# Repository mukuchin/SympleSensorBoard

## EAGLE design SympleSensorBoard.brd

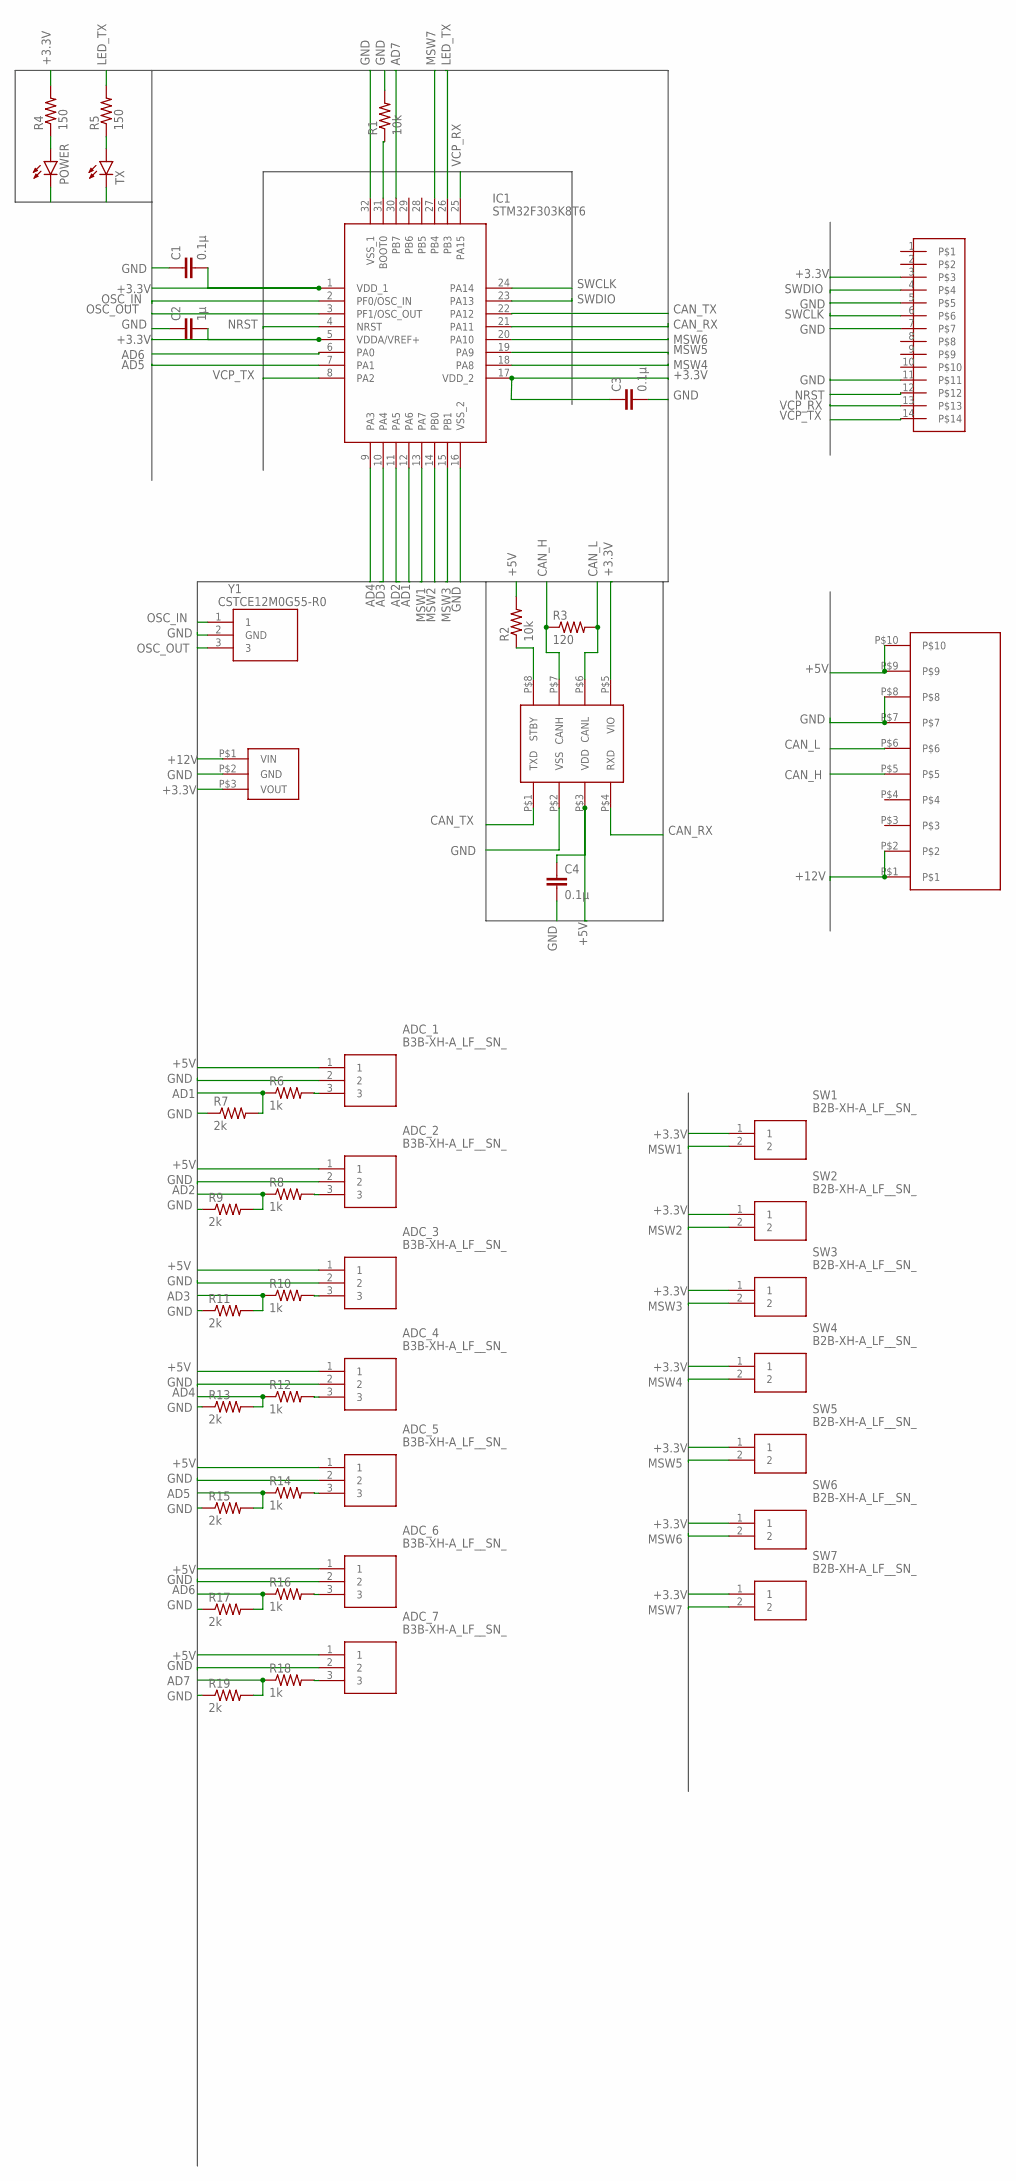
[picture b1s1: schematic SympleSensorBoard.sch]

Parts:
ADC_1, ADC_2, ADC_3, ADC_4, ADC_5, ADC_6, ADC_7: B3B-XH-A_LF__SN_; SHDR3W64P0X250_1X3_990X575X700
C1, C3, C4: 0.1μ; C0603
C2: 1μ; C0603
IC1: STM32F303K8T6; QFP80P900X900X160-32N
POWER: LEDCHIP-LED0603; CHIP-LED0603
R1, R2: 10k; R0603
R3: 120; R0603
R4, R5: 150; R0603
R6, R8, R10, R12, R14, R16, R18: 1k; R0603
R7, R9, R11, R13, R15, R17, R19: 2k; R0603
SW1, SW2, SW3, SW4, SW5, SW6, SW7: B2B-XH-A_LF__SN_; SHDR2W64P0X250_1X2_740X575X700
TX: LEDCHIP-LED0603; CHIP-LED0603
U$1: BP5293-33; DC/DC_REGULATOR_3P
U$2: MCP2562MCP2561-SN; SOIC8
U$3: BOX14P; CON_HEDA14P_1.27
U$4: BOX10PBOX10P-L; BOX10P-L
Y1: CSTCE12M0G55-R0

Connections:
+3.3V: C1.2, C2.2, C3.1, IC1.1 (VDD_1), IC1.5 (VDDA/VREF+), IC1.17 (VDD_2), R4.2, SW1.1, SW2.1, SW3.1, SW4.1, SW5.1, SW6.1, SW7.1, U$1.P$3 (VOUT), U$2.P$5 (VIO), U$3.3
+5V: ADC_1.1, ADC_2.1, ADC_3.1, ADC_4.1, ADC_5.1, ADC_6.1, ADC_7.1, C4.1, R2.2, U$2.P$3 (VDD), U$4.P$9, U$4.P$10
+12V: U$1.P$1 (VIN), U$4.P$1, U$4.P$2
AD1: IC1.12 (PA6), R6.1, R7.2
AD2: IC1.11 (PA5), R8.1, R9.2
AD3: IC1.10 (PA4), R10.1, R11.2
AD4: IC1.9 (PA3), R12.1, R13.2
AD5: IC1.7 (PA1), R14.1, R15.2
AD6: IC1.6 (PA0), R16.1, R17.2
AD7: IC1.30 (PB7), R18.1, R19.2
CAN_H: R3.1, U$2.P$7 (CANH), U$4.P$5
CAN_L: R3.2, U$2.P$6 (CANL), U$4.P$6
CAN_RX: IC1.21 (PA11), U$2.P$4 (RXD)
CAN_TX: IC1.22 (PA12), U$2.P$1 (TXD)
GND: ADC_1.2, ADC_2.2, ADC_3.2, ADC_4.2, ADC_5.2, ADC_6.2, ADC_7.2, C1.1, C2.1, C3.2, C4.2, IC1.16 (VSS_2), IC1.32 (VSS_1), POWER.C, R1.2, R7.1, R9.1, R11.1, R13.1, R15.1, R17.1, R19.1, TX.C, U$1.P$2 (GND), U$2.P$2 (VSS), U$3.5, U$3.7, U$3.11, U$4.P$7, U$4.P$8, Y1.2 (GND)
LED_TX: IC1.26 (PB3), R5.2
MSW1: IC1.13 (PA7), SW1.2
MSW2: IC1.14 (PB0), SW2.2
MSW3: IC1.15 (PB1), SW3.2
MSW4: IC1.18 (PA8), SW4.2
MSW5: IC1.19 (PA9), SW5.2
MSW6: IC1.20 (PA10), SW6.2
MSW7: IC1.27 (PB4), SW7.2
unnamed: IC1.31 (BOOT0), R1.1
unnamed: R2.1, U$2.P$8 (STBY)
unnamed: POWER.A, R4.1
unnamed: R5.1, TX.A
unnamed: ADC_1.3, R6.2
unnamed: ADC_2.3, R8.2
unnamed: ADC_3.3, R10.2
unnamed: ADC_4.3, R12.2
unnamed: ADC_5.3, R14.2
unnamed: ADC_6.3, R16.2
unnamed: ADC_7.3, R18.2
NRST: IC1.4 (NRST), U$3.12
OSC_IN: IC1.2 (PF0/OSC_IN), Y1.1
OSC_OUT: IC1.3 (PF1/OSC_OUT), Y1.3
SWCLK: IC1.24 (PA14), U$3.6
SWDIO: IC1.23 (PA13), U$3.4
VCP_RX: IC1.25 (PA15), U$3.13
VCP_TX: IC1.8 (PA2), U$3.14

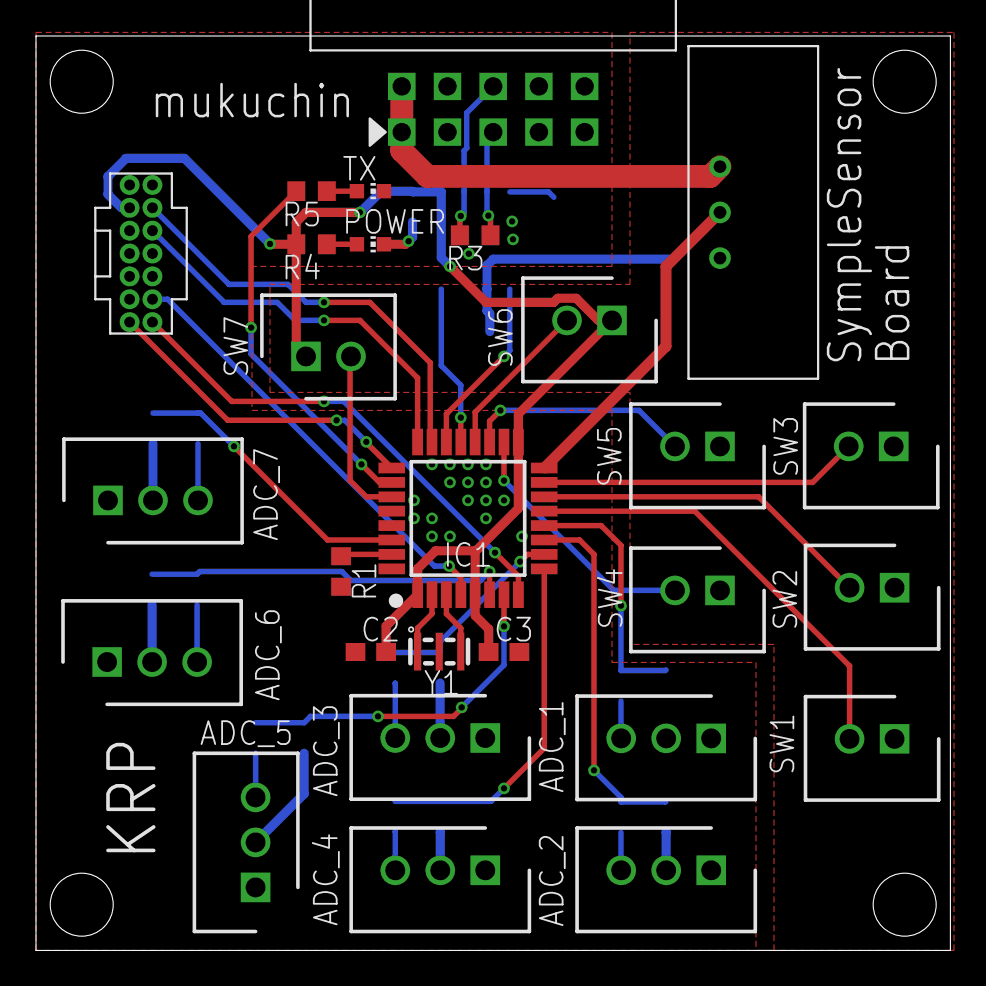
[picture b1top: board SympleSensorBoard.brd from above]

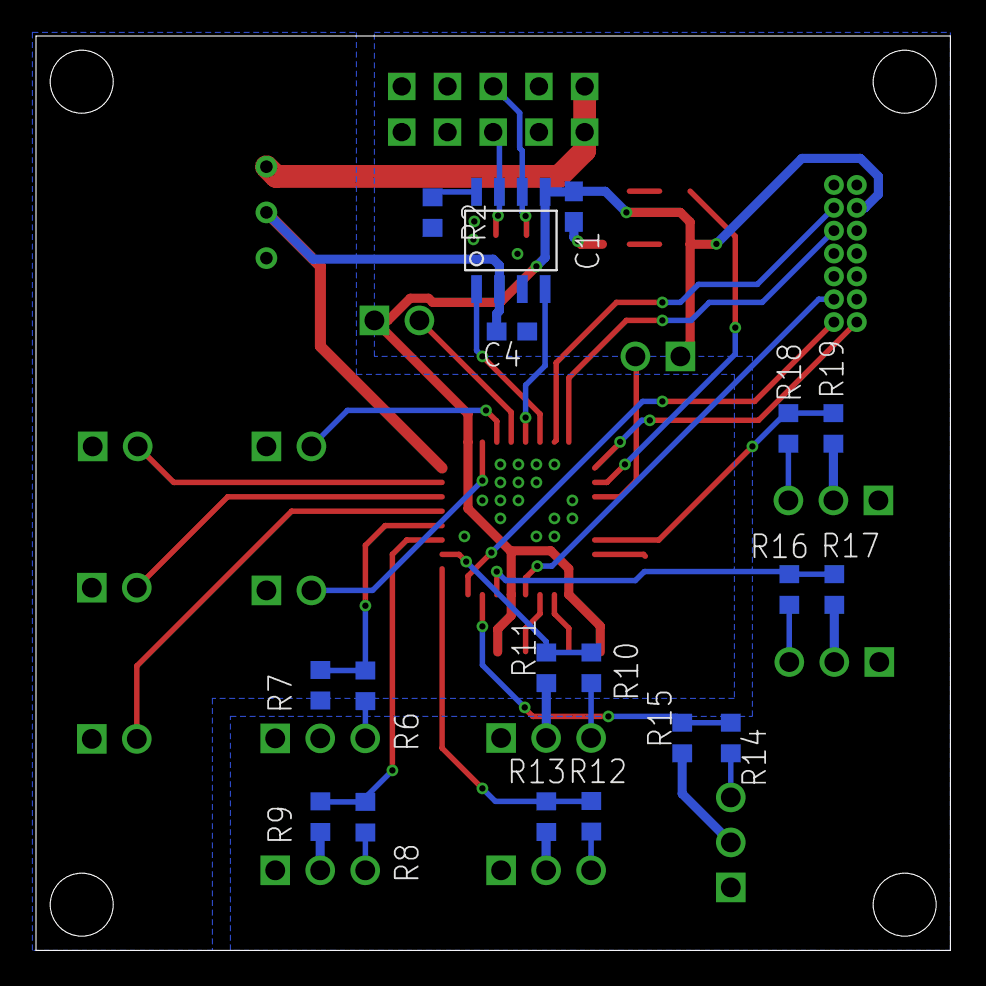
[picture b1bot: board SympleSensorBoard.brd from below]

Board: 2 copper layers, 50.8 x 50.8 mm, 45 parts (18 on the bottom side), 41 nets.

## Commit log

2020-11-03 回路図が途中です
2020-11-04 回路図完成しました
2020-11-12 .sch、.brd共に完成
2020-11-16 コネクタ位置の修正、コネクタ番号を基盤上に表示、部品の再配置、再配線完了。使うセンサはまだ決まっていない。
2020-11-20 I2Cコネクタを全て外した。I2Cは別の基盤で行う。
2020-11-24 部品リスト作りました。
2020-11-27 10ピンコネクタのホールの大きさを修正した
